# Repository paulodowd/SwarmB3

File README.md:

# SwarmB3

Working on Swarm Board version 3... so I decided the tinkering hadn't finished yet :)

Currently work in progress.  
- PCB in testing, version 4.
- Initial code drafted but a mess.

## Development Notes

**14/04/26:** Lots and lots of debugging between hardware and software.  The pcb design worked on the assumption that the UART tx could be inverted in software, as stated in the SAMD51 datasheet.  However, it doesn't work as I expected.  It seems to invert the data, but the idle state remains high.  This causes issues for IR communication because I don't want to saturate the environment with the carrier wave whilst communication is not occuring (idle high, AND'd with clock -> constant carrier wave transmission). I tried a software fix, pulling the gpio low between transmissions.  However, I can't seem to restore the GPIO properly without messing up the protocol overall. I got as far as seeing the bit pattern shifted by 1 bit, which is occuring because the receiver is mis-registering the start bit.  I tried leaving the GPIO alone, and only enabling/disabling the carrier wave, but the same problem is occuring.  When I look at both sides of the communication on the oscilloscope, I can see that for a batch send (like 10 bytes), the first byte is dropping the start bit.  I haven't been able to get to the bottom of why.  If I do not invert the tx, the problem goes away, but I don't want a non-inverted signal (saturation problem).  It could be that the essential problem is that inverting the Tx in SAMD51 doesn't invert the start and stop bits - the datasheet is unclear.  It simply says "start and stop unchanged", and I'm not sure if that means overall functionality or logic polarity.  It seems like the latter.  I tried some other logic gates.  Surprisingly, 74hc32 (OR) works as a drop in - however, it does mean that for data logic 1, the data stream is always on, and for data logic 0 actually an on/off pulse train - which is not ideal.  The receiver seems quite robust to this, the datasheet has measures for this sort of thing.  However, I don't want a board that could cause communication defects alongside from what I am investigating in research.  A possible fix is to implement active low LED drivers, which would necessitate an extra transister per UART (e.g. +4).  I don't fancy soldering that, so instead I've updated the pcb to pass tx outputs through a 74hc14 first.  I've tested this on breadboard and it works fine.  It means I can just use the UART interfaces normally without any software SAMD51 inversion.  The current code (ItsyBitsy_test) is a mess from all my debugging chopping and changes.  I'll refactor after testing the new pcb when it arrives.

**10/04/26:** The TSDP34156 is active low output when receiving an IR burst.  I had thought I would use the M4 SERCOM interface to invert the UART signal logic.  It seems like only the start,stop and data are inverted, but the idle signal remains high in either case. I spent some time trying to find a software solution to pull the tx line low, with no luck.  Even with no idle, or long bursts of transmission, I was getting gibberish on the receiving end regardless of whether I was inverting Tx or not.  With the assumption of inverting in software, the first pcb design had a 74hc08 AND gate to combine the 58khz clock and data.  Abandoning this, I first tried a NAND, but that actually just negates the effect of the clock - since a changing clock qualifies as not-and against data or no data.  Instead, an OR gate works. With Tx not inverted, if I draw out the truth table, then it means that for a data logic 0 a 58khz burst is created, and for data logic 1 a constant IR signal is made (not modulated, just on).     

**08/04/26:** Some pretty annoying problems with the first PCB prototype!  The 74hc08 ground was isolated.  The pots for current limiting were not in logical physical locations, not next to their LEDs.  I labelled the ItsyBitsy pin 7 wrong, so it wasn't conencted to the 74hc08.  Fixed all of that.  I've installed two different types of IR LEDs to compare the difference.  One is the Vishay TSAL4400 (https://www.vishay.com/en/product/81006/), and the other is an Onsemi QEE113 (https://www.onsemi.com/products/interfaces/infrared/emitting-diodes/qee113).  Both have similar characteristics, slightly different radiance patterns. I prefer the form factor of the Onsemi device.

**27/03/26:** Using the Adafruit SAMD51 board config, they have a wrapped class named sercom around the original defintions SERCOM (difference being lower and upper case).  I wanted to invert Tx (maybe Rx) and the Adafruit wrapper hasn't got this implemented yet.  These are useful links for low level structures and definitions for SERCOM (SAMD51 in general).
- https://github.com/ace22293/SAMD51/tree/master
- https://github.com/arduino/ArduinoCore-samd/tree/master/cores/arduino
- https://github.com/arduino/ArduinoModule-CMSIS-Atmel/tree/master/CMSIS-Atmel/CMSIS/Device/ATMEL/samd51/include/instance
- https://github.com/arduino/ArduinoModule-CMSIS-Atmel/tree/master/CMSIS-Atmel/CMSIS/Device/ATMEL/samd51/include

- **25/03/26:** Started the design of version 3 of the swarm board.  The plan is to use the Adafruit ItsyBitsy M4, providing a hardware UART interface for each IR reciever on the pcb. When drafting this PCB, I couldn't find a convenient symbol or footprint, so I've used two rows of pin headers and labels.  I also noticed that the symbol for the double row header for the M5Stack Core2 doesn't correspond with the physical footprint - but the enumeration is correct (just a bit confusing).

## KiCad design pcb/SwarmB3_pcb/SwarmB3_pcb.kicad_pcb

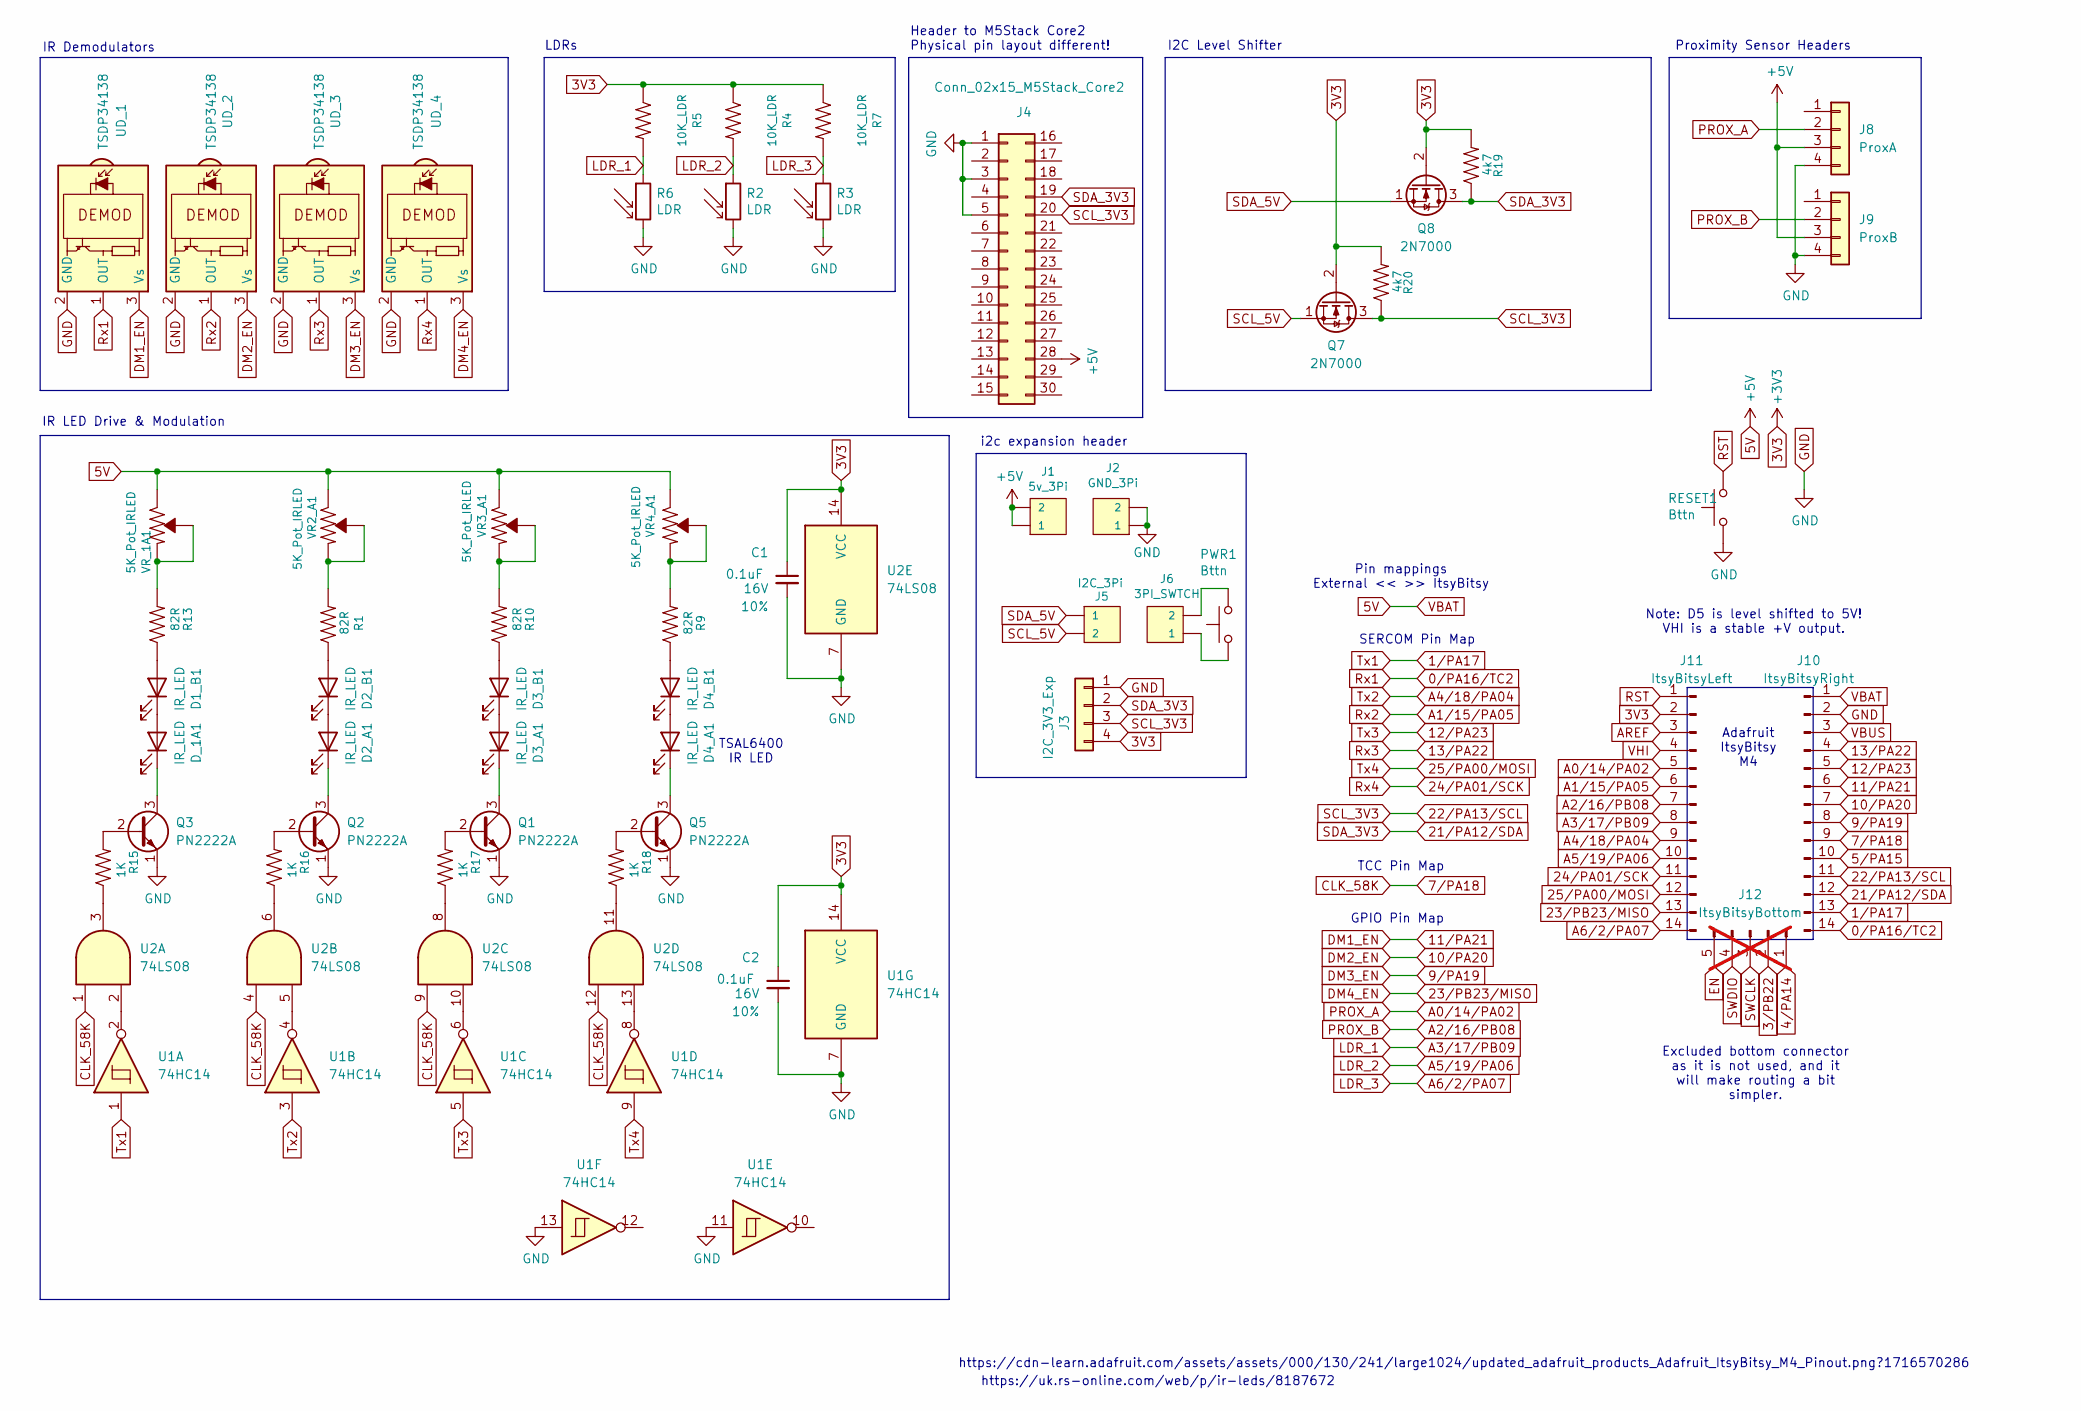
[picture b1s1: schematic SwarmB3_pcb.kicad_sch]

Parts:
C1, C2: 0.1uF; C_Disc_D4.7mm_W2.5mm_P5.00mm; Voltage 16V; Tolerance 10%
D1_B1, D2_A1, D2_B1, D3_A1, D3_B1, D4_A1, D4_B1: IR_LED; LED_D3.0mm_Horizontal_O1.27mm_Z2.0mm
D_1A1: IR_LED; LED_D3.0mm_Horizontal_O1.27mm_Z2.0mm
J1: 5v_3Pi; PinHeader_1x02_P2.54mm_Vertical
J2: GND_3Pi; PinHeader_1x02_P2.54mm_Vertical
J3: I2C_3V3_Exp; PinHeader_1x04_P2.54mm_Vertical
J4: Conn_02x15_M5Stack_Core2; PinHeader_2x15_P2.54mm_Vertical
J5: I2C_3Pi; PinHeader_1x02_P2.54mm_Vertical
J6: 3PI_SWTCH; PinHeader_1x02_P2.54mm_Vertical
J8: ProxA; PinHeader_1x04_P2.54mm_Vertical
J9: ProxB; PinHeader_1x04_P2.54mm_Vertical
J10: ItsyBitsyRight; PinHeader_1x14_P2.54mm_Vertical
J11: ItsyBitsyLeft; PinHeader_1x14_P2.54mm_Vertical
J12: ItsyBitsyBottom; not fitted
PWR1: Bttn; SW_PUSH_6mm
Q1, Q2, Q3, Q5: PN2222A; TO-92_Inline
Q7, Q8: 2N7000; TO-92_Inline
R1, R9, R10, R13: 82R; R_Axial_DIN0204_L3.6mm_D1.6mm_P7.62mm_Horizontal
R2, R3, R6: LDR; R_LDR_5.0x4.1mm_P3mm_Vertical
R4, R5, R7: 10K_LDR; R_Axial_DIN0204_L3.6mm_D1.6mm_P7.62mm_Horizontal
R15, R16, R17, R18: 1K; R_Axial_DIN0204_L3.6mm_D1.6mm_P7.62mm_Horizontal
R19, R20: 4k7; R_Axial_DIN0204_L3.6mm_D1.6mm_P7.62mm_Horizontal
RESET1: Bttn; SW_PUSH_6mm
U1: 74HC14; DIP-14_W7.62mm_Socket
U2: 74LS08; DIP-14_W7.62mm_Socket
UD_1, UD_2, UD_3, UD_4: TSDP34138; Vishay_MOLD-3Pin
VR2_A1, VR3_A1, VR4_A1: 5K_Pot_IRLED; Potentiometer_Bourns_3386P_Vertical
VR_1A1: 5K_Pot_IRLED; Potentiometer_Bourns_3386P_Vertical

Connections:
0/PA16/TC2: J10.14, UD_1.1 (OUT)
1/PA17: J10.13, U1.1
3V3: C1.1, C2.1, J3.4, J11.2, Q7.2 (G), Q8.2 (G), R4.1, R5.1, R7.1, R19.2, R20.2, U1.14 (VCC), U2.14 (VCC)
5V: J1.1, J1.2, J4.28, J8.3, J9.3, J10.1, VR2_A1.3 (CW), VR3_A1.3 (CW), VR4_A1.3 (CW), VR_1A1.3 (CW)
5/PA15: J10.10
7/PA18: J10.9, U2.1, U2.4, U2.9, U2.12
9/PA19: J10.8, UD_3.3 (Vs)
10/PA20: J10.7, UD_2.3 (Vs)
11/PA21: J10.6, UD_1.3 (Vs)
12/PA23: J10.5, U1.5
13/PA22: J10.4, UD_3.1 (OUT)
21/PA12/SDA: J3.2, J4.19, J10.12, Q8.3 (D), R19.1
22/PA13/SCL: J3.3, J4.20, J10.11, Q7.3 (D), R20.1
23/PB23/MISO: J11.13, UD_4.3 (Vs)
24/PA01/SCK: J11.11, UD_4.1 (OUT)
25/PA00/MOSI: J11.12, U1.9
A0/14/PA02: J8.2, J11.5
A1/15/PA05: J11.6, UD_2.1 (OUT)
A2/16/PB08: J9.2, J11.7
A3/17/PB09: J11.8, R5.2, R6.1
A4/18/PA04: J11.9, U1.3
A5/19/PA06: J11.10, R2.1, R4.2
A6/2/PA07: J11.14, R3.1, R7.2
AREF: J11.3
GND: C1.2, C2.2, J2.1, J2.2, J3.1, J4.1, J4.3, J4.5, J8.4, J9.4, J10.2, Q1.1 (E), Q2.1 (E), Q3.1 (E), Q5.1 (E), R2.2, R3.2, R6.2, RESET1.1, U1.7 (GND), U1.11, U1.13, U2.7 (GND), UD_1.2 (GND), UD_2.2 (GND), UD_3.2 (GND), UD_4.2 (GND)
unnamed: D1_B1.2 (A), R13.1
unnamed: D1_B1.1 (K), D_1A1.2 (A)
unnamed: D2_A1.2 (A), D2_B1.1 (K)
unnamed: D2_A1.1 (K), Q2.3 (C)
unnamed: D2_B1.2 (A), R1.1
unnamed: D3_A1.2 (A), D3_B1.1 (K)
unnamed: D3_A1.1 (K), Q1.3 (C)
unnamed: D3_B1.2 (A), R10.1
unnamed: D4_A1.2 (A), D4_B1.1 (K)
unnamed: D4_A1.1 (K), Q5.3 (C)
unnamed: D4_B1.2 (A), R9.1
unnamed: D_1A1.1 (K), Q3.3 (C)
unnamed: J6.1, PWR1.1
unnamed: J6.2, PWR1.2
unnamed: Q1.2 (B), R17.2
unnamed: Q2.2 (B), R16.2
unnamed: Q3.2 (B), R15.2
unnamed: Q5.2 (B), R18.2
unnamed: R15.1, U2.3
unnamed: R16.1, U2.6
unnamed: R17.1, U2.8
unnamed: R18.1, U2.11
unnamed: U1.2, U2.2
unnamed: U1.4, U2.5
unnamed: U1.6, U2.10
unnamed: U1.8, U2.13
unnamed: R1.2, VR2_A1.1 (CCW), VR2_A1.2 (WIPER)
unnamed: R10.2, VR3_A1.1 (CCW), VR3_A1.2 (WIPER)
unnamed: R9.2, VR4_A1.1 (CCW), VR4_A1.2 (WIPER)
unnamed: R13.2, VR_1A1.1 (CCW), VR_1A1.2 (WIPER)
RST: J11.1, RESET1.2
SCL_5V: J5.2, Q7.1 (S)
SDA_5V: J5.1, Q8.1 (S)
VBUS: J10.3
VHI: J11.4

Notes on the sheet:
IR LED Drive & Modulation
IR Demodulators
Pin mappings External << >> ItsyBitsy
Proximity Sensor Headers
GPIO Pin Map
I2C Level Shifter
Adafruit ItsyBitsy M4
SERCOM Pin Map
Header to M5Stack Core2 Physical pin layout different!
https://uk.rs-online.com/web/p/ir-leds/8187672
TCC Pin Map
Note: D5 is level shifted to 5V! VHI is a stable +V output.
https://cdn-learn.adafruit.com/assets/assets/000/130/241/large1024/updated_adafruit_products_Adafruit_ItsyBitsy_M4_Pinout.png?1716570286
LDRs
Excluded bottom connector as it is not used, and it will make routing a bit simpler.
i2c expansion header
TSAL6400 IR LED

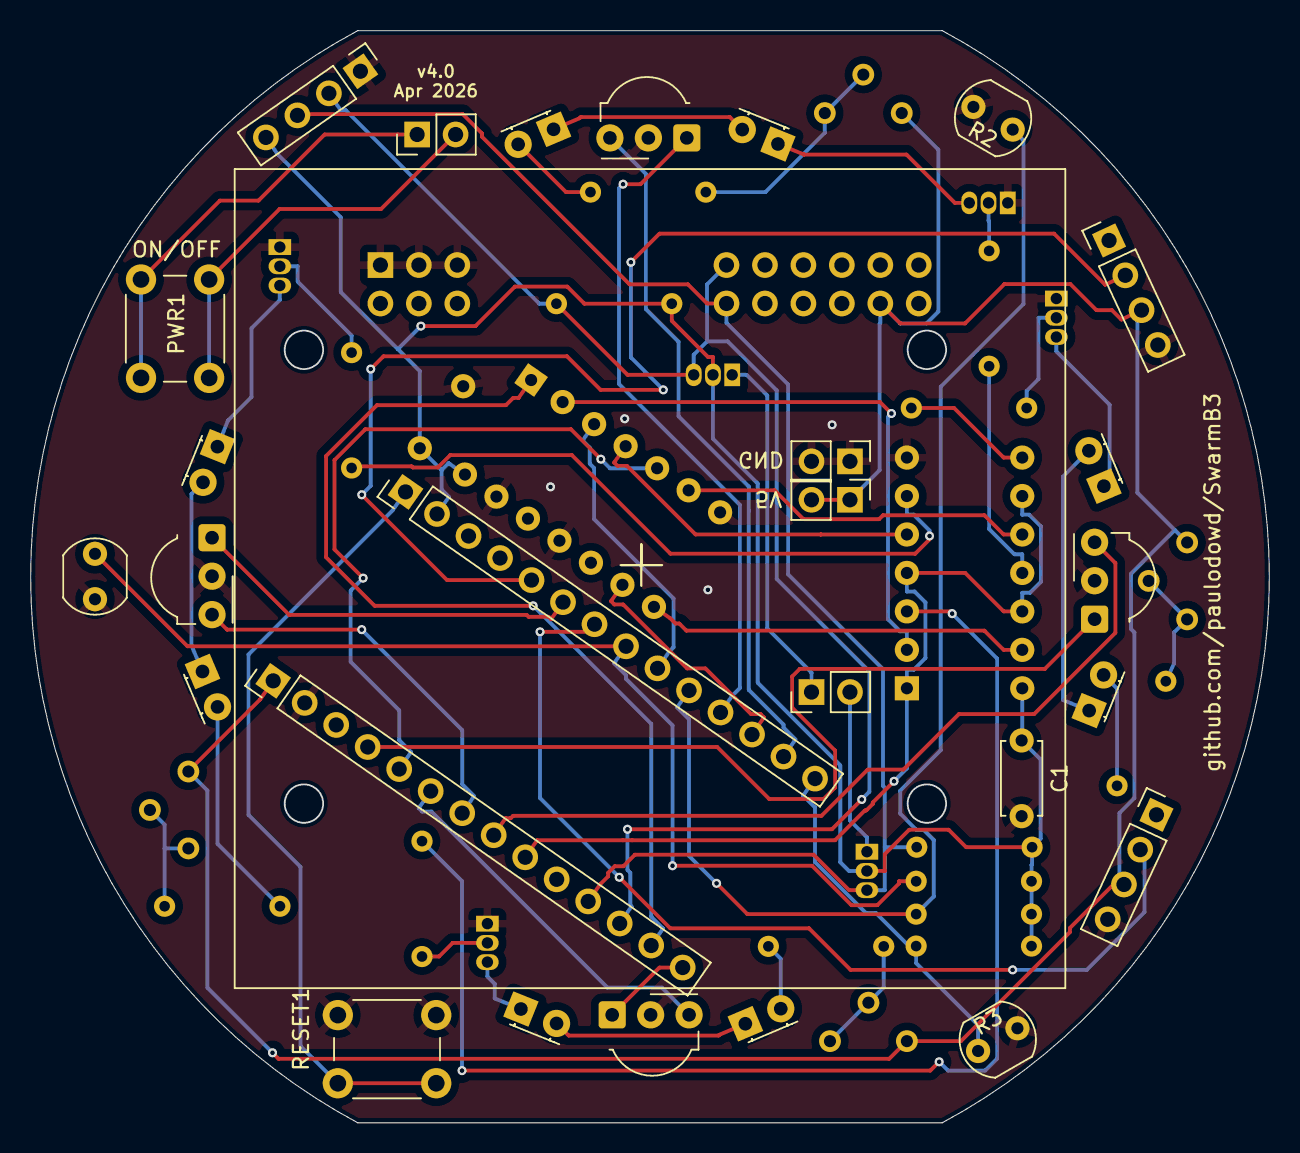
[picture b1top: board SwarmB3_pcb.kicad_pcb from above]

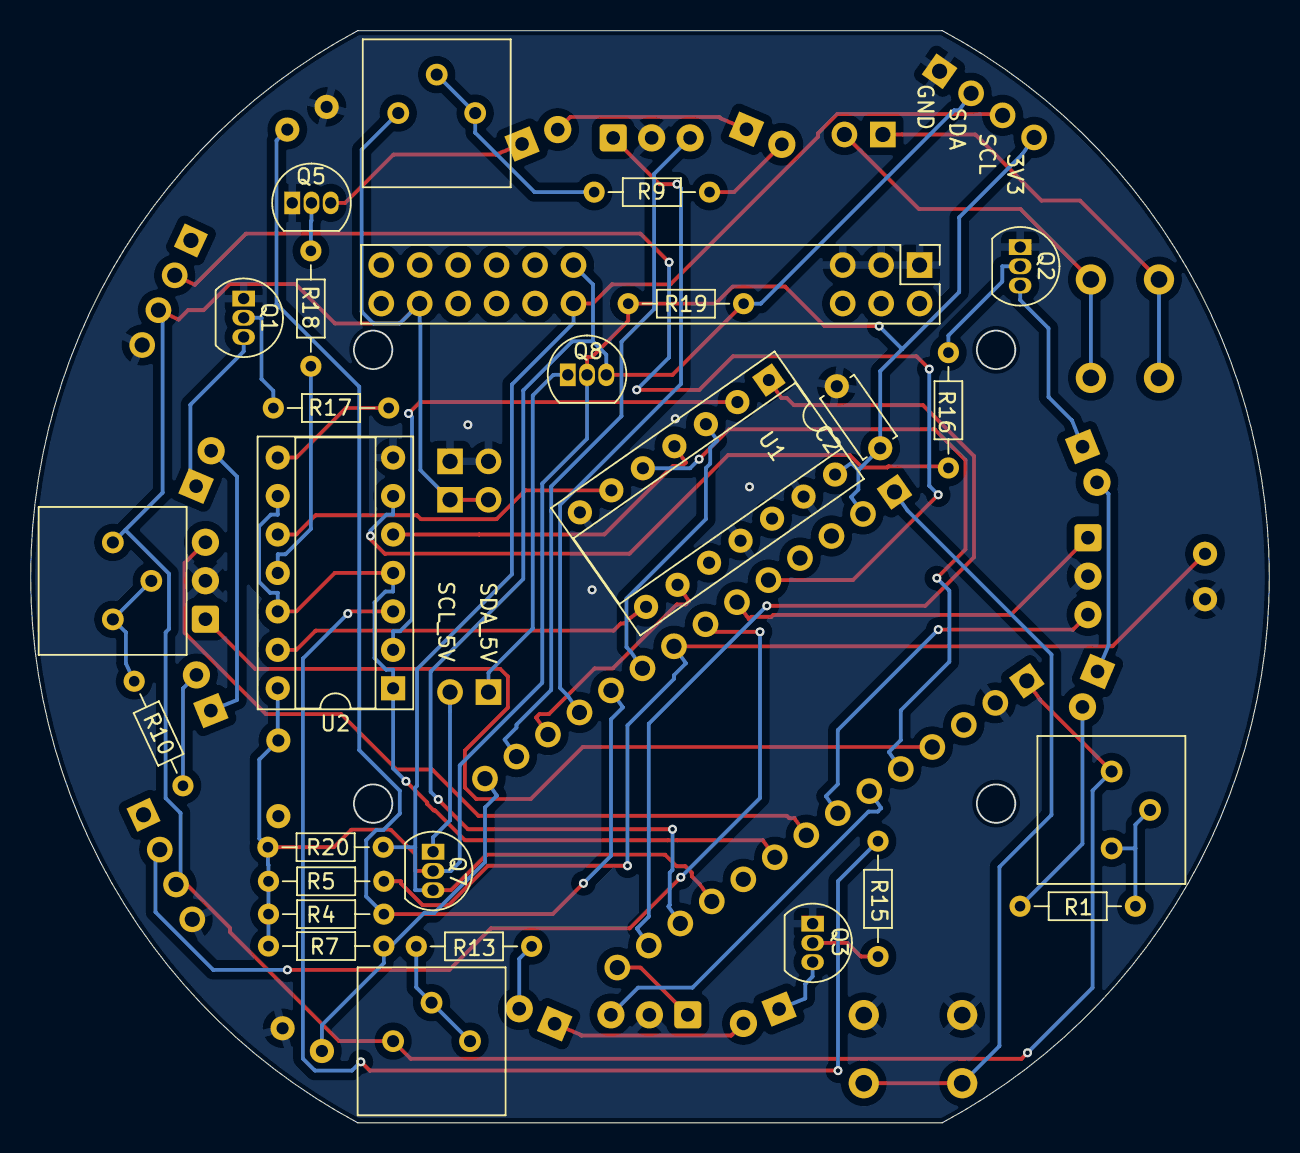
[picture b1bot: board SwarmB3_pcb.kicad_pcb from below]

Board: 2 copper layers, 81.7 x 72.1 mm, 54 parts (27 on the bottom side), 56 nets.

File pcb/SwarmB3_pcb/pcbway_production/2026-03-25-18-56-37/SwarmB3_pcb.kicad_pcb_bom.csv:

Designator,Quantity,Value,Footprint,Package,MPN,DNP,Mount_Type,Description,PROD_ID,Voltage,Tolerance,Field4
C1,1,0.1uF,C_Disc_D4.7mm_W2.5mm_P5.00mm,,,,tht,Unpolarized capacitor,CAP-25565,16V,10%,
"D1_B1, D2_A1, D2_B1, D3_A1, D3_B1, D4_A1, D4_B1, D_1A1",8,IR_LED,LED_D3.0mm_Horizontal_O1.27mm_Z2.0mm,,,,tht,,,,,
J1,1,5v_3Pi,PinHeader_1x02_P2.54mm_Vertical,,,,tht,,,,,CONN-09863
J10,1,ItsyBitsyRight,PinHeader_1x14_P2.54mm_Vertical,,,,tht,"Generic connector, single row, 01x14, script generated",,,,
J11,1,ItsyBitsyLeft,PinHeader_1x14_P2.54mm_Vertical,,,,tht,"Generic connector, single row, 01x14, script generated",,,,
J2,1,GND_3Pi,PinHeader_1x02_P2.54mm_Vertical,,,,tht,,,,,CONN-09863
J3,1,I2C_3V3_Exp,PinHeader_1x04_P2.54mm_Vertical,,,,tht,,,,,
J4,1,Conn_02x15_M5Stack_Core2,PinHeader_2x15_P2.54mm_Vertical,,,,tht,,,,,
J5,1,I2C_3Pi,PinHeader_1x02_P2.54mm_Vertical,,,,tht,,,,,CONN-09863
J6,1,3PI_SWTCH,PinHeader_1x02_P2.54mm_Vertical,,,,tht,,,,,CONN-09863
J8,1,ProxA,PinHeader_1x04_P2.54mm_Vertical,,,,tht,,,,,
J9,1,ProxB,PinHeader_1x04_P2.54mm_Vertical,,,,tht,,,,,
"PWR1, RESET",2,Bttn,SW_PUSH_6mm,,,,tht,,,,,
"Q1, Q2, Q3, Q5",4,PN2222A,TO-92_Inline,,,,tht,"1A Ic, 40V Vce, NPN Transistor, General Purpose Transistor, TO-92",,,,
"Q7, Q8",2,2N7000,TO-92_Inline,,,,tht,,,,,
"R1, R10, R13, R9",4,82R,R_Axial_DIN0204_L3.6mm_D1.6mm_P7.62mm_Horizontal,,,,tht,,,,, 
"R15, R16, R17, R18",4,1K,R_Axial_DIN0204_L3.6mm_D1.6mm_P7.62mm_Horizontal,,,,tht,,,,, 
"R19, R20",2,4k7,R_Axial_DIN0204_L3.6mm_D1.6mm_P7.62mm_Horizontal,,,,tht,,,,, 
"R2, R3, R6",3,LDR,R_LDR_5.0x4.1mm_P3mm_Vertical,,,,tht,,,,,
"R4, R5, R7",3,10K_LDR,R_Axial_DIN0204_L3.6mm_D1.6mm_P7.62mm_Horizontal,,,,tht,,,,, 
U1,1,74LS08,DIP-14_W7.62mm_Socket,,,,tht,Quad And2,,,,
"UD_1, UD_2, UD_3, UD_4",4,TSDP34138,Vishay_MOLD-3Pin,,,,tht,,,,,
"VR2_A1, VR3_A1, VR4_A1, VR_1A1",4,5K_Pot_IRLED,Potentiometer_Bourns_3386P_Vertical,,,,tht,,,,,RES-09730

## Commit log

2026-03-25 pcb design prior to prototyping
2026-03-25 added some development notes, removed old files
2026-03-27 add initial test code for itsybitsy
2026-03-27 updated dev log
2026-03-27 Implemented frame error counting and helpers.
2026-03-28 stripping back and rationalising the datatypes/structures for this new board where we no longer need to poll receivers. That means timing information for rx is now obsolete. The only thing that matte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
2026-03-30 Counldn't get SERCOM0 to work with standard approach. Had to do a manual init then use the Arduino Uart class afterwards. Tested working. Daisy chained tx to rx around all 4 uart interfaces.
2026-03-30 sercom0 fix intergrated with ItsyBitsy_test, minor bug in setup stopped SerialD12 rx from working
2026-03-31 tested i2c on default pins and a 58khz signal on pin 7, both working.
2026-04-01 moved sercom functions into their own source files.
2026-04-08 Found errors with the PCB, fixed. Pin 7 was labelled wrong, so it wasn't connected to the 74HC08. 3 of the pots were located in illogical places, not next to the associated LEDs. The 74HC08 was also 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
2026-04-08 Revise development notes for swarm board version 3
    Updated development notes for version 3 of the swarm board, detailing issues with the first PCB prototype and comparisons of IR LEDs.
2026-04-09 Somehow, I had the pcb manufactured with A1 as rx for a UART, but my latest design files were for A5. Since I've debugged and tested the PCB as working, I've modified the design files back to using A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
2026-04-14 Lots and lots of debugging between hardware and software. The pcb design worked on the assumption that the UART tx could be inverted in software, as stated in the SAMD51 datasheet. However, it doesn'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
2026-04-14 devlog update
2026-04-24 add in non-blocking functionality to toggle the demodulators on and off for a short period to remove the effect of the automatic gain control saturating when there is no carrier signal. ALtered the p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
2026-04-24 Fixed a bug with the parser getNextByte() function. For any intermediate byte in a payload, it wasn't returning a 1-byte value, meaning that the activity log was always too few. I could see a 9 byte 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
2026-04-25 cleaned up config.h, then implemented calls to the config through the code. Implemented disabling Rx during a transmit. Implemented non-blocking transmit. Decided to add a 3rd demod state, so active,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
2026-04-25 added a todo list for next time, added baud to the config.
2026-04-26 Converted tx_timings timestamps back to milliseconds. I think we are getting roughly 1ms per byte transmitted out of UART, and I don't think higher precision than that is useful. I've started to impl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
2026-04-26 broadcast transmit framework in
2026-04-26 Found an interesting limitation I hadn't considered with Swarm-B2. The Serial.write() function is blocking whilst there are not enough bytes free in the buffer. I don't want this operation to block. 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
2026-04-27 implemented and test broadcast tx and individual tx. Implemented tx timing configuration and desync - both tested. Implemented defer but not yet tested. Implemented rx overrun but not yet tested. Ove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
2026-04-27 tested all functionality. Seems to be working. The remaining task is to populate the i2c request/receive functions. Built a second board and tested transmit between them. Small refactor, moved all ma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
2026-04-29 implemented i2c functionality. Tested against a master side SwarmB3_c class implementation to make i2c calls. Not everything is fully tested yet. Message sending and receiving is tested. Getting conf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
2026-04-30 preparing to merge in refactor1 branch
2026-04-30 forgot to rename .ino file in firmware
2026-04-30 caught a bug: had the wrong SERCOM identified in the frame count ISR for D0/D1 (SERCOM3). Also had a related bug in the i2cUpdateFrameCount() function. Implemented Pololu side functions to read over 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
2026-04-30 updated pololu side to start running some tests and capturing data
2026-04-30 added a new i2c data struct to count both the instances of transmission and the instances of deferred transmission. Tested working on the pololu side.
2026-05-04 implemented an exponential back off for defer, it might be good to update the variables from defer to csma. Needs testing.
2026-05-10 Caught a bug when the board was configured for broadcast. memcpy was used from 0 to other channels, but the for loop stopped 1 short.
2026-05-11 Found and fixed an interesting bug. When doing a broadcast transmission, the function attemptMsgWriteToSerialBuffer() was filling up the entire serial buffer, and this was taking up to approx 250us. 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
2026-05-13 Issue#3: amended the IRParser_c class to include the CRC in the escaping. Tested working.
2026-05-13 moved byte time out check in parser class over to microseconds, and so changed timeout_multi config parameter to be multiples of 100us. Found a bug with b_masked, fixed that.
